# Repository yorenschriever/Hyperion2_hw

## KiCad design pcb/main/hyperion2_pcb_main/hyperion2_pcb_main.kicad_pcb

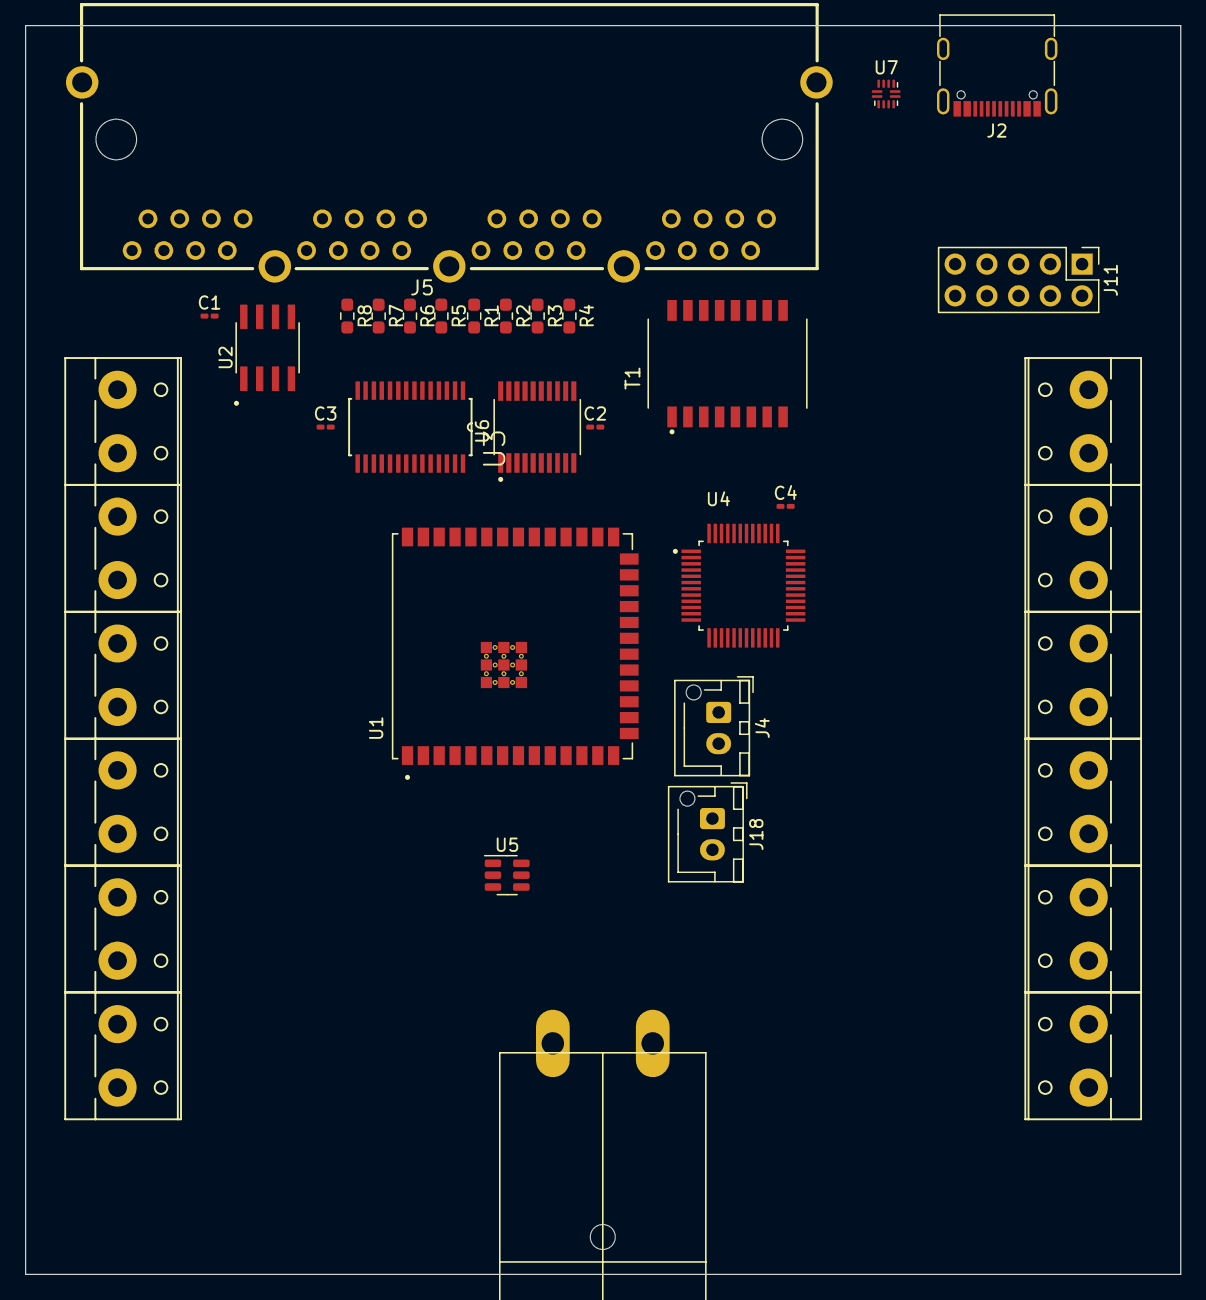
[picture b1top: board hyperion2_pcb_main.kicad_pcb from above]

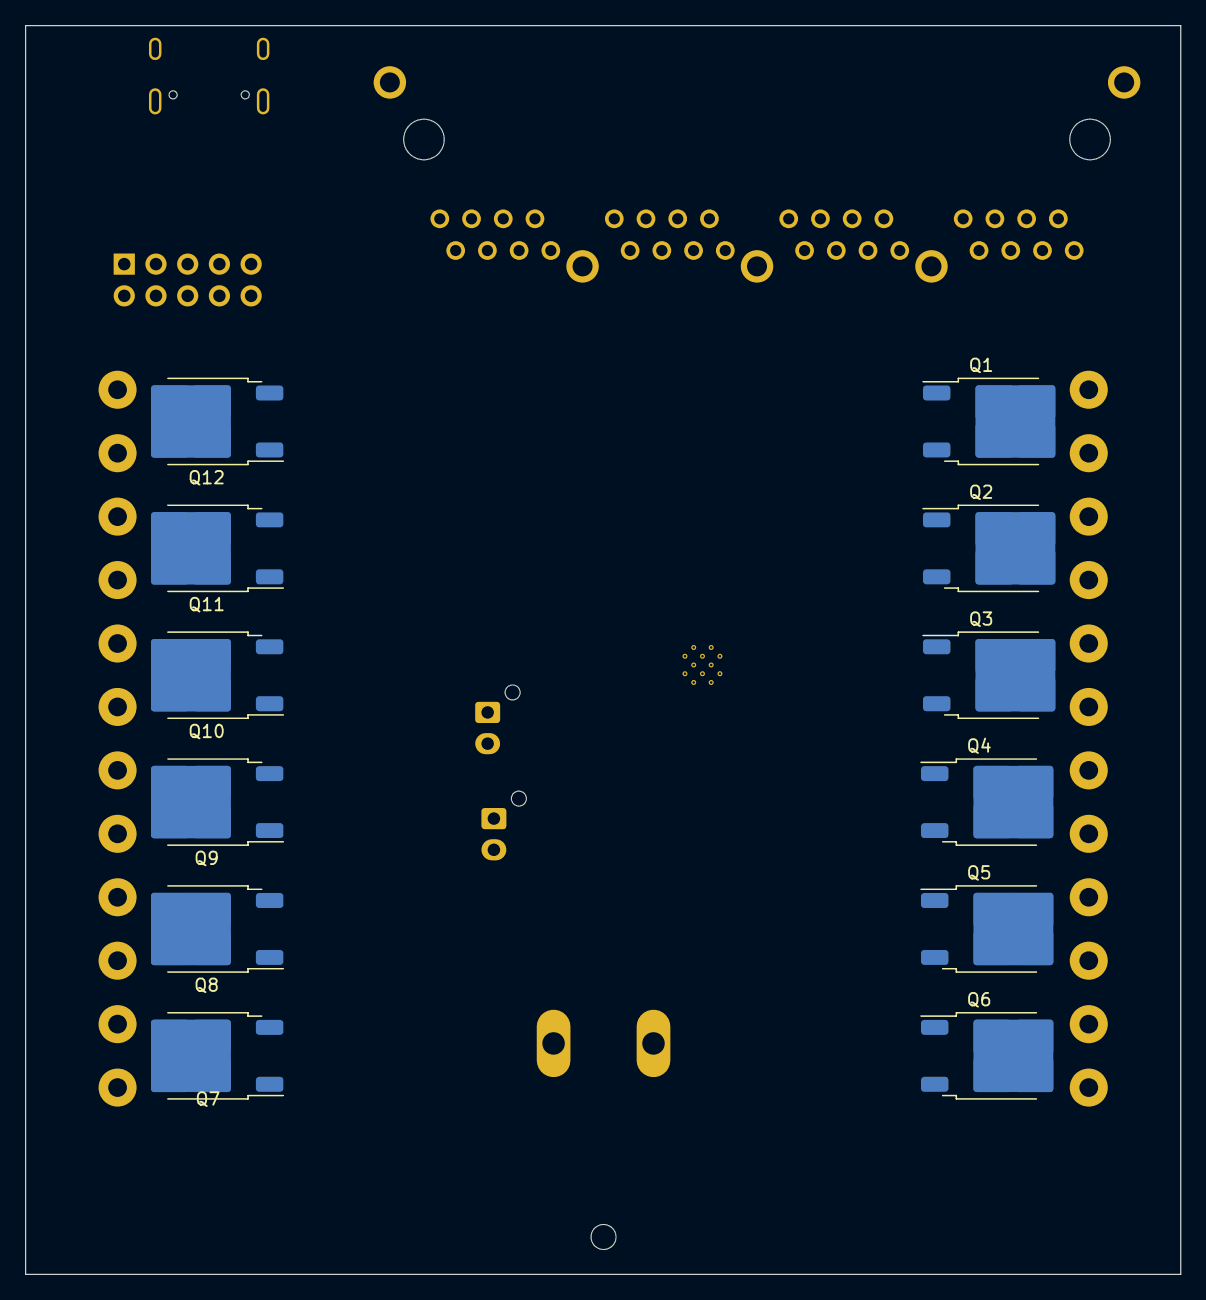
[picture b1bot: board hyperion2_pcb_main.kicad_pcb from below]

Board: 4 copper layers, 92.5 x 100.0 mm, 50 parts (12 on the bottom side), 59 nets, no tracks yet.

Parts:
C1, C2, C3, C4: 100nF; C_0201_0603Metric_Pad0.64x0.40mm_HandSolder
J1, J6, J7, J8, J9, J10, J12, J13, J14, J15, J16, J17: Screw_Terminal_01x02; CON-WAGO-508_W237-132PLUGGABLE
J2: USB_C_Receptacle_USB2.0; USB_C_Receptacle_G-Switch_GT-USB-7010ASV
J3: Barrel_Jack; POWERPOLEPCBMOUNT
J4, J18: Barrel_Jack; JST_XH_B2B-XH-AM_1x02_P2.50mm_Vertical
J5: 8P8C_Shielded; CONN-TH_DS1129-02-S80BP
J11: Panel; PinHeader_2x05_P2.54mm_Vertical
Q1, Q2, Q3, Q4, Q5, Q6, Q7, Q8, Q9, Q10, Q11, Q12: NCV8401; TO-252-2
R1, R2, R3, R4, R5, R6, R7, R8: 100R; R_0603_1608Metric_Pad0.98x0.95mm_HandSolder
T1: H1102NLT; XFMR_H1102NLT
U1: ESP32-S3-WROOM-1U-N16R8; XCVR_ESP32-S3-WROOM-1U-N16R8
U2: MAX3488ECSA_; SOIC127P600X175-8N
U3: PCA9685PW_118; SOP65P640X110-28N
U4: W5500; QFP50P900X900X160-48N
U5: LMR16006YQ5; SOT-23-6
U6: SN74HCT245PWR; SOP65P640X120-20N
U7: TUSB320; Texas_X2QFN-12_1.6x1.6mm_P0.4mm

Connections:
+3V3: C1.1, C3.1, C4.1, J11.1, J18.1, U2.1 (VCC)
+5V: C2.1, U6.1 (DIR), U6.20 (VCC)
/DMXA: J5.D3, U2.8 (A)
/DMXB: J5.D6, U2.7 (B)
/DMXY: J5.D1, U2.5 (Y)
/DMXZ: J5.D2, U2.6 (Z)
GND: C1.2, C2.2, C3.2, C4.2, J3.2, J4.2, J5.B1, J5.B3, J5.B5, J5.B7, J5.C1, J5.C3, J5.C5, J5.C7, J5.D4, J5.D5, J5.D7, J5.D8, J5.EH, J11.2, J18.2, Q1.3 (S), Q2.3 (S), Q3.3 (S), Q4.3 (S), Q5.3 (S), Q6.3 (S), Q7.3 (S), Q8.3 (S), Q9.3 (S), Q10.3 (S), Q11.3 (S), Q12.3 (S), U2.4 (GND), U6.10 (GND), U6.19 (~OE)
unnamed: J1.2, Q9.2 (D)
unnamed: J2.A5 (CC1), U7.1 (CC1)
unnamed: J2.B5 (CC2), U7.2 (CC2)
unnamed: J2.A1 (GND), J2.A12 (GND), J2.B1 (GND), J2.B12 (GND)
unnamed: J5.A1, T1.16
unnamed: J5.A2, T1.14
unnamed: J5.A3, T1.11
unnamed: J5.A6, T1.9
unnamed: J5.B2, R4.1
unnamed: J5.B4, R3.1
unnamed: J5.B6, R2.1
unnamed: J5.B8, R1.1
unnamed: J5.C2, R5.1
unnamed: J5.C4, R6.1
unnamed: J5.C6, R7.1
unnamed: J5.C8, R8.1
unnamed: J6.2, Q2.2 (D)
unnamed: J7.2, Q3.2 (D)
unnamed: J8.2, Q4.2 (D)
unnamed: J9.2, Q5.2 (D)
unnamed: J10.2, Q6.2 (D)
unnamed: J12.2, Q1.2 (D)
unnamed: J13.2, Q7.2 (D)
unnamed: J14.2, Q8.2 (D)
unnamed: J15.2, Q10.2 (D)
unnamed: J16.2, Q11.2 (D)
unnamed: J17.2, Q12.2 (D)
unnamed: U1.1 (GND), U1.40 (GND), U1.41_1 (GND), U1.41_2 (GND), U1.41_3 (GND), U1.41_4 (GND), U1.41_5 (GND), U1.41_6 (GND), U1.41_7 (GND), U1.41_8 (GND), U1.41_9 (GND)
unnamed: U1.17 (IO9), U4.32 (~SCSN)
unnamed: U1.18 (IO10), U4.33 (SCLK)
unnamed: U1.19 (IO11), U4.34 (MISO)
unnamed: U1.20 (IO12), U4.35 (MOSI)
unnamed: U1.21 (IO13), U4.36 (~INTN)
unnamed: U1.22 (IO14), U4.37 (~RSTN)
unnamed: J2.A7 (D-), J2.B7 (D-), U1.13 (IO19)
unnamed: J2.A6 (D+), J2.B6 (D+), U1.14 (IO20)
unnamed: U4.3 (AGND), U4.9 (AGND), U4.14 (AGND), U4.16 (AGND), U4.19 (AGND), U4.48 (AGND)
unnamed: U4.4 (AVDD), U4.8 (AVDD), U4.11 (AVDD), U4.15 (AVDD), U4.17 (AVDD), U4.21 (AVDD)
unnamed: T1.8, U4.5 (RXN)
unnamed: T1.6, U4.6 (RXP)
unnamed: T1.3, U4.1 (TXN)
unnamed: T1.1, U4.2 (TXP)
unnamed: R8.2, U6.18 (B1)
unnamed: R7.2, U6.17 (B2)
unnamed: R6.2, U6.16 (B3)
unnamed: R5.2, U6.15 (B4)
unnamed: R1.2, U6.14 (B5)
unnamed: R2.2, U6.13 (B6)
unnamed: R3.2, U6.12 (B7)
unnamed: R4.2, U6.11 (B8)
unnamed: J2.A4 (VBUS), J2.A9 (VBUS), J2.B4 (VBUS), J2.B9 (VBUS), U7.4 (VBUS_DET)
VDD: J1.1, J3.1, J4.1, J6.1, J7.1, J8.1, J9.1, J10.1, J12.1, J13.1, J14.1, J15.1, J16.1, J17.1

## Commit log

2023-10-01 initial commit: first components
2023-10-01 placed more components
2023-10-10 board size, placement of connectors
2023-10-10 panel connector
2023-10-11 exact alignment with v1 pcb
